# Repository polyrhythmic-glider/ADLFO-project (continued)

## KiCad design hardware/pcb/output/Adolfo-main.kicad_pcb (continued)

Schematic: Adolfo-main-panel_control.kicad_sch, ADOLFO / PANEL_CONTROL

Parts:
R41: 10k; r0805

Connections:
+3V3: R41.2; also elsewhere on the board
OLED_RESET: R41.1; also elsewhere on the board

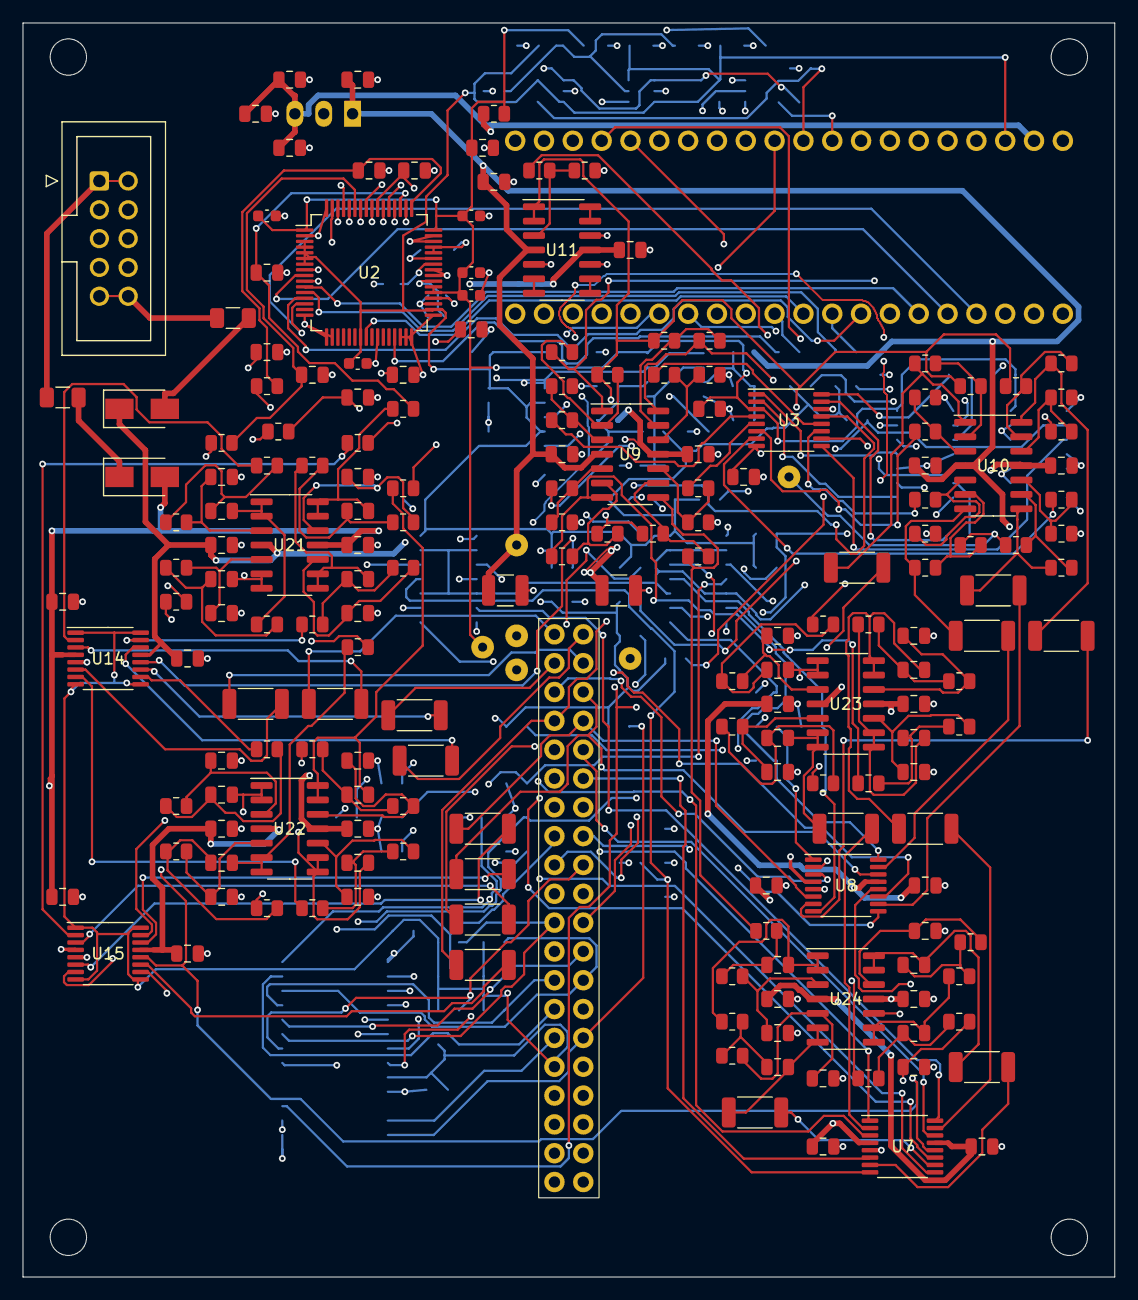
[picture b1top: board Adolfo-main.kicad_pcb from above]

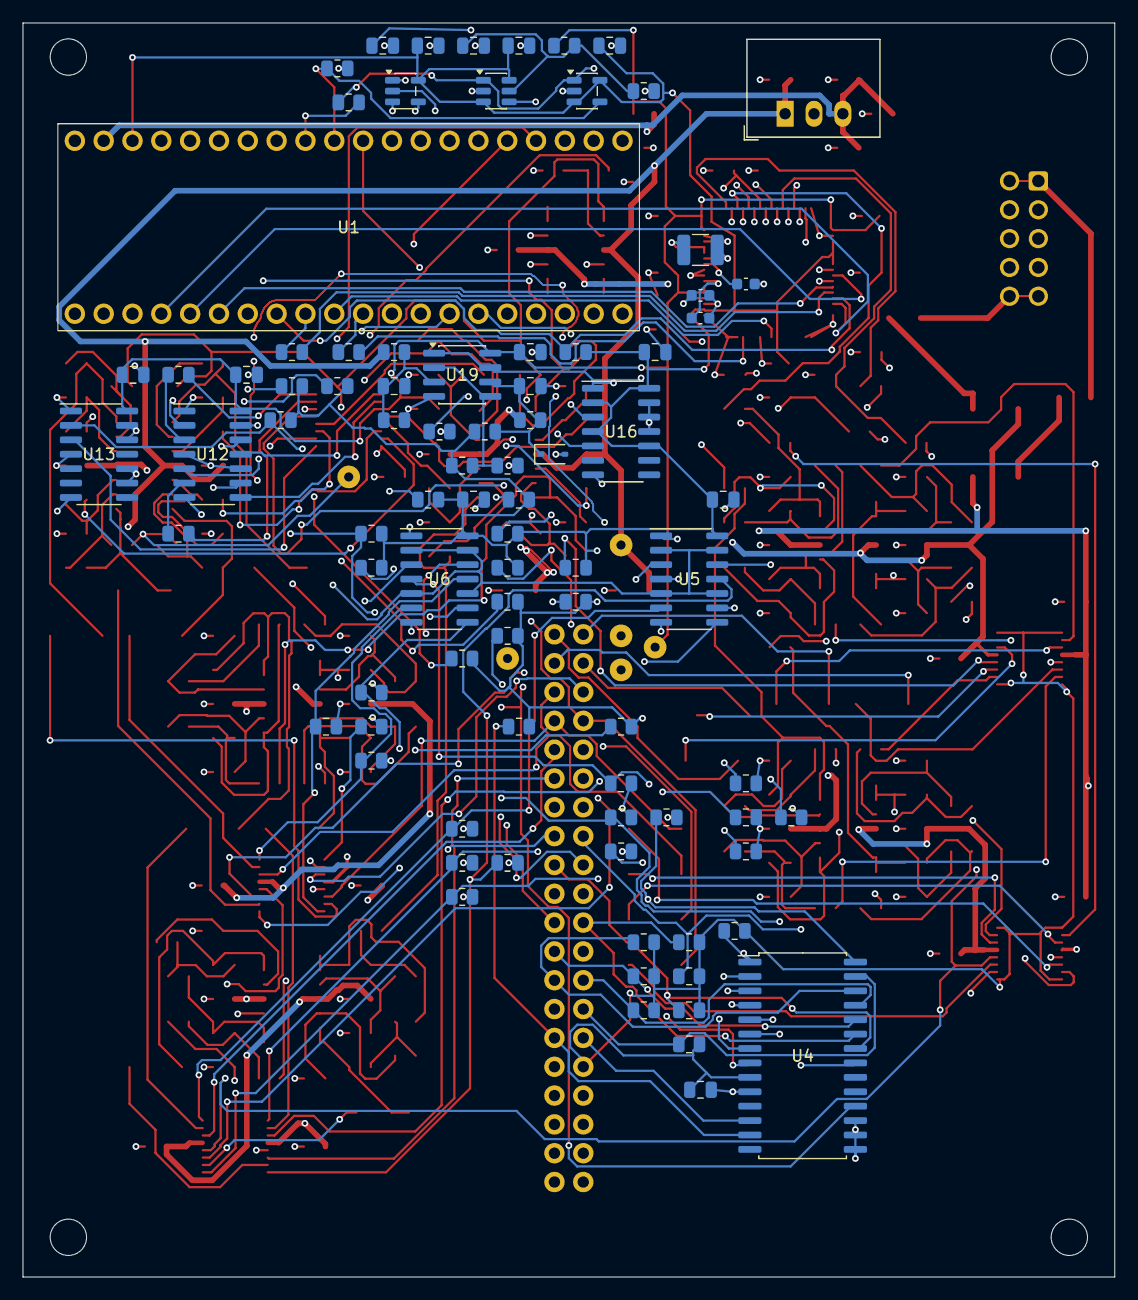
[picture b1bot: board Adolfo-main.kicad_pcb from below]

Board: 4 copper layers, 96.2 x 110.5 mm, 283 parts (87 on the bottom side), 212 nets.

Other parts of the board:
H1, H2, H3, H4: mount

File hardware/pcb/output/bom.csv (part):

Reference,Circuit role,Value / part,Footprint,Board,Side,X,Y,Notes,MPN,Manufacturer,Datasheet
J13,JM,Samtec TSW-120-07-G-D,header40,main,F,50.6,87,,,,
J15,JP,Samtec SSW-120-02-G-D,socket40,panel,B,50.6,87,Mirrored socket numbering mates to JM pin-for-pin.,,,
E1,E1,ALPS EC11E18244AU,encoder,panel,F,17.5,48,,,,
K1,K1,E-Switch TL1105DF160Q,button,panel,F,17.5,67,,,,
J1,J1,IN1 PJ398SM,jack,panel,F,17.5,80,Fixed IN normal grounded for a defined unpatched input; CTRL/OUT normals open to avoid shorting an output.,,,
J2,J2,CTRL1 PJ398SM,jack,panel,F,17.5,95,Fixed IN normal grounded for a defined unpatched input; CTRL/OUT normals open to avoid shorting an output.,,,
J3,J3,OUT1 PJ398SM,jack,panel,F,17.5,110,Fixed IN normal grounded for a defined unpatched input; CTRL/OUT normals open to avoid shorting an output.,,,
E2,E2,ALPS EC11E18244AU,encoder,panel,F,39.5,48,,,,
K2,K2,E-Switch TL1105DF160Q,button,panel,F,39.5,67,,,,
J4,J4,IN2 PJ398SM,jack,panel,F,39.5,80,Fixed IN normal grounded for a defined unpatched input; CTRL/OUT normals open to avoid shorting an output.,,,
J5,J5,CTRL2 PJ398SM,jack,panel,F,39.5,95,Fixed IN normal grounded for a defined unpatched input; CTRL/OUT normals open to avoid shorting an output.,,,
J6,J6,OUT2 PJ398SM,jack,panel,F,39.5,110,Fixed IN normal grounded for a defined unpatched input; CTRL/OUT normals open to avoid shorting an output.,,,
E3,E3,ALPS EC11E18244AU,encoder,panel,F,61.5,48,,,,
K3,K3,E-Switch TL1105DF160Q,button,panel,F,61.5,67,,,,
J7,J7,IN3 PJ398SM,jack,panel,F,61.5,80,Fixed IN normal grounded for a defined unpatched input; CTRL/OUT normals open to avoid shorting an output.,,,
J8,J8,CTRL3 PJ398SM,jack,panel,F,61.5,95,Fixed IN normal grounded for a defined unpatched input; CTRL/OUT normals open to avoid shorting an output.,,,
J9,J9,OUT3 PJ398SM,jack,panel,F,61.5,110,Fixed IN normal grounded for a defined unpatched input; CTRL/OUT normals open to avoid shorting an output.,,,
E4,E4,ALPS EC11E18244AU,encoder,panel,F,83.5,48,,,,
K4,K4,E-Switch TL1105DF160Q,button,panel,F,83.5,67,,,,
J10,J10,IN4 PJ398SM,jack,panel,F,83.5,80,Fixed IN normal grounded for a defined unpatched input; CTRL/OUT normals open to avoid shorting an output.,,,
J11,J11,CTRL4 PJ398SM,jack,panel,F,83.5,95,Fixed IN normal grounded for a defined unpatched input; CTRL/OUT normals open to avoid shorting an output.,,,
J12,J12,OUT4 PJ398SM,jack,panel,F,83.5,110,Fixed IN normal grounded for a defined unpatched input; CTRL/OUT normals open to avoid shorting an output.,,,
J14,J14,"Waveshare 0.96inch OLED Module (D), I2C",oled7,panel,F,50.6,11,"Waveshare module (D), SSD1315, 26 x 26 mm; I2C hardware configuration required. Seven-pin order VCC/GND/DIN/CLK/CS/DC/RES.",,,
U1,U1,Daisy Seed 3,seed,main,B,70,27,Seed 3 40-pin carrier; onboard codec and MCU DAC unused. Verify physical USB access on the assembled stack.,,,
U2,U2,AD7606C-18BSTZ,lqfp64,main,F,33,31,"SOFTWARE mode OS[2:0]=111; select one DOUTA, bipolar ranges, bandwidth per channel. No audio HPF. Register/DMA driver missing.",AD7606C-18BSTZ,Analog Devices,https://www.analog.com/media/en/technical-documentation/data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
U3,U3,DAC8568BPW,tssop16,main,F,70,44,"B grade matters: internal 2.5 V reference, output span 2.5 V, midscale reset; enable reference in software. 16-bit output, not a 24-bit codec.",DAC8568BPW,Texas Instruments,https://www.ti.com/lit/ds/symlink/dac8568.pdf
U4,U4,MCP23017-E/SO,soic28,main,B,30,100,I2C 0x20. Encoders A/B stay on MCU GPIO; only clicks/keys and static output requests use expander.,MCP23017-E/SO,Microchip,https://ww1.microchip.com/downloads/en/DeviceDoc/20001952C.pdf
U5,U5,SN74LVC08ADR,soic14,main,B,40,58,,SN74LVC08ADR,Texas Instruments,https://www.ti.com/lit/ds/symlink/sn74lvc08a.pdf
U6,U6,SN74LVC08ADR,soic14,main,B,62,58,,SN74LVC08ADR,Texas Instruments,https://www.ti.com/lit/ds/symlink/sn74lvc08a.pdf
U7,U7,ADG5412FBRUZ,tssop16,main,F,80,108,Not ADG5413F. IN=0 disconnects. Protected S faces jack; driver on D. Fault/power-off isolation needs bench qualification; not protection against every output collision.,ADG5412FBRUZ,Analog Devices,https://www.analog.com/media/en/technical-documentation/data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
U8,U8,ADG5412FBRUZ,tssop16,main,F,75,85,Not ADG5413F. IN=0 disconnects. Protected S faces jack; driver on D. Fault/power-off isolation needs bench qualification; not protection against every output collision.,ADG5412FBRUZ,Analog Devices,https://www.analog.com/media/en/technical-documentation/data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
RA1,RA1,10k 0.1%,r0805,main,F,50,44,,,,
RB1,RB1,40k 0.1%,r0805,main,F,50,41,,,,
RC1,RC1,10k 0.1%,r0805,main,F,54,40,,,,
RD1,RD1,40k 0.1%,r0805,main,F,50,38,,,,
RO1,RO1,1k 1W 1%,r2010,main,F,75,80,Limits fault current; specify/calibrate the intended load. Not a load-independent pitch output.,CRCW20101K00FKEFHP,Vishay,https://www.vishay.com/docs/20043/crcwhpe3.pdf
RE1,RE1,100k,r0805,main,B,60,83,,,,
RQ1,RQ1,100k,r0805,main,B,35,79,,,,
RA2,RA2,10k 0.1%,r0805,main,F,50,50,,,,
RB2,RB2,40k 0.1%,r0805,main,F,50,53,,,,
RC2,RC2,10k 0.1%,r0805,main,F,54,54,,,,
RD2,RD2,40k 0.1%,r0805,main,F,50,56,,,,
RO2,RO2,1k 1W 1%,r2010,main,F,82,80,Limits fault current; specify/calibrate the intended load. Not a load-independent pitch output.,CRCW20101K00FKEFHP,Vishay,https://www.vishay.com/docs/20043/crcwhpe3.pdf
RE2,RE2,100k,r0805,main,B,60,80,,,,
RQ2,RQ2,100k,r0805,main,B,35,76,,,,
RA3,RA3,10k 0.1%,r0805,main,F,62,50,,,,
RB3,RB3,40k 0.1%,r0805,main,F,62,53,,,,
RC3,RC3,10k 0.1%,r0805,main,F,58,54,,,,
RD3,RD3,40k 0.1%,r0805,main,F,62,56,,,,
RO3,RO3,1k 1W 1%,r2010,main,F,67,105,Limits fault current; specify/calibrate the intended load. Not a load-independent pitch output.,CRCW20101K00FKEFHP,Vishay,https://www.vishay.com/docs/20043/crcwhpe3.pdf
RE3,RE3,100k,r0805,main,B,60,86,,,,
RQ3,RQ3,100k,r0805,main,B,35,82,,,,
RA4,RA4,10k 0.1%,r0805,main,F,59,40,,,,
RB4,RB4,40k 0.1%,r0805,main,F,63,40,,,,
RC4,RC4,10k 0.1%,r0805,main,F,59,37,,,,
RD4,RD4,40k 0.1%,r0805,main,F,63,37,,,,
RO4,RO4,1k 1W 1%,r2010,main,F,87,101,Limits fault current; specify/calibrate the intended load. Not a load-independent pitch output.,CRCW20101K00FKEFHP,Vishay,https://www.vishay.com/docs/20043/crcwhpe3.pdf
RE4,RE4,100k,r0805,main,B,56,83,,,,
RQ4,RQ4,100k,r0805,main,B,31,79,,,,
RA5,RA5,10k 0.1%,r0805,main,F,82,45,,,,
RB5,RB5,40k 0.1%,r0805,main,F,82,42,,,,
RC5,RC5,10k 0.1%,r0805,main,F,86,41,,,,
RD5,RD5,40k 0.1%,r0805,main,F,82,39,,,,
RO5,RO5,1k 1W 1%,r2010,main,F,76,57,Limits fault current; specify/calibrate the intended load. Not a load-independent pitch output.,CRCW20101K00FKEFHP,Vishay,https://www.vishay.com/docs/20043/crcwhpe3.pdf
RE5,RE5,100k,r0805,main,B,68,71,,,,
RQ5,RQ5,100k,r0805,main,B,46,79,,,,
RA6,RA6,10k 0.1%,r0805,main,F,82,51,,,,
RB6,RB6,40k 0.1%,r0805,main,F,82,54,,,,
RC6,RC6,10k 0.1%,r0805,main,F,86,55,,,,
RD6,RD6,40k 0.1%,r0805,main,F,82,57,,,,
RO6,RO6,1k 1W 1%,r2010,main,F,87,63,Limits fault current; specify/calibrate the intended load. Not a load-independent pitch output.,CRCW20101K00FKEFHP,Vishay,https://www.vishay.com/docs/20043/crcwhpe3.pdf
RE6,RE6,100k,r0805,main,B,68,74,,,,
RQ6,RQ6,100k,r0805,main,B,46,76,,,,
RA7,RA7,10k 0.1%,r0805,main,F,94,51,,,,
RB7,RB7,40k 0.1%,r0805,main,F,94,54,,,,
RC7,RC7,10k 0.1%,r0805,main,F,90,55,,,,
RD7,RD7,40k 0.1%,r0805,main,F,94,57,,,,
RO7,RO7,1k 1W 1%,r2010,main,F,88,59,Limits fault current; specify/calibrate the intended load. Not a load-independent pitch output.,CRCW20101K00FKEFHP,Vishay,https://www.vishay.com/docs/20043/crcwhpe3.pdf
RE7,RE7,100k,r0805,main,B,68,68,,,,
RQ7,RQ7,100k,r0805,main,B,46,82,,,,
RA8,RA8,10k 0.1%,r0805,main,F,94,45,,,,
RB8,RB8,40k 0.1%,r0805,main,F,94,42,,,,
RC8,RC8,10k 0.1%,r0805,main,F,90,41,,,,
RD8,RD8,40k 0.1%,r0805,main,F,94,39,,,,
RO8,RO8,1k 1W 1%,r2010,main,F,94,63,Limits fault current; specify/calibrate the intended load. Not a load-independent pitch output.,CRCW20101K00FKEFHP,Vishay,https://www.vishay.com/docs/20043/crcwhpe3.pdf
RE8,RE8,100k,r0805,main,B,72,71,,,,
RQ8,RQ8,100k,r0805,main,B,42,79,,,,
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
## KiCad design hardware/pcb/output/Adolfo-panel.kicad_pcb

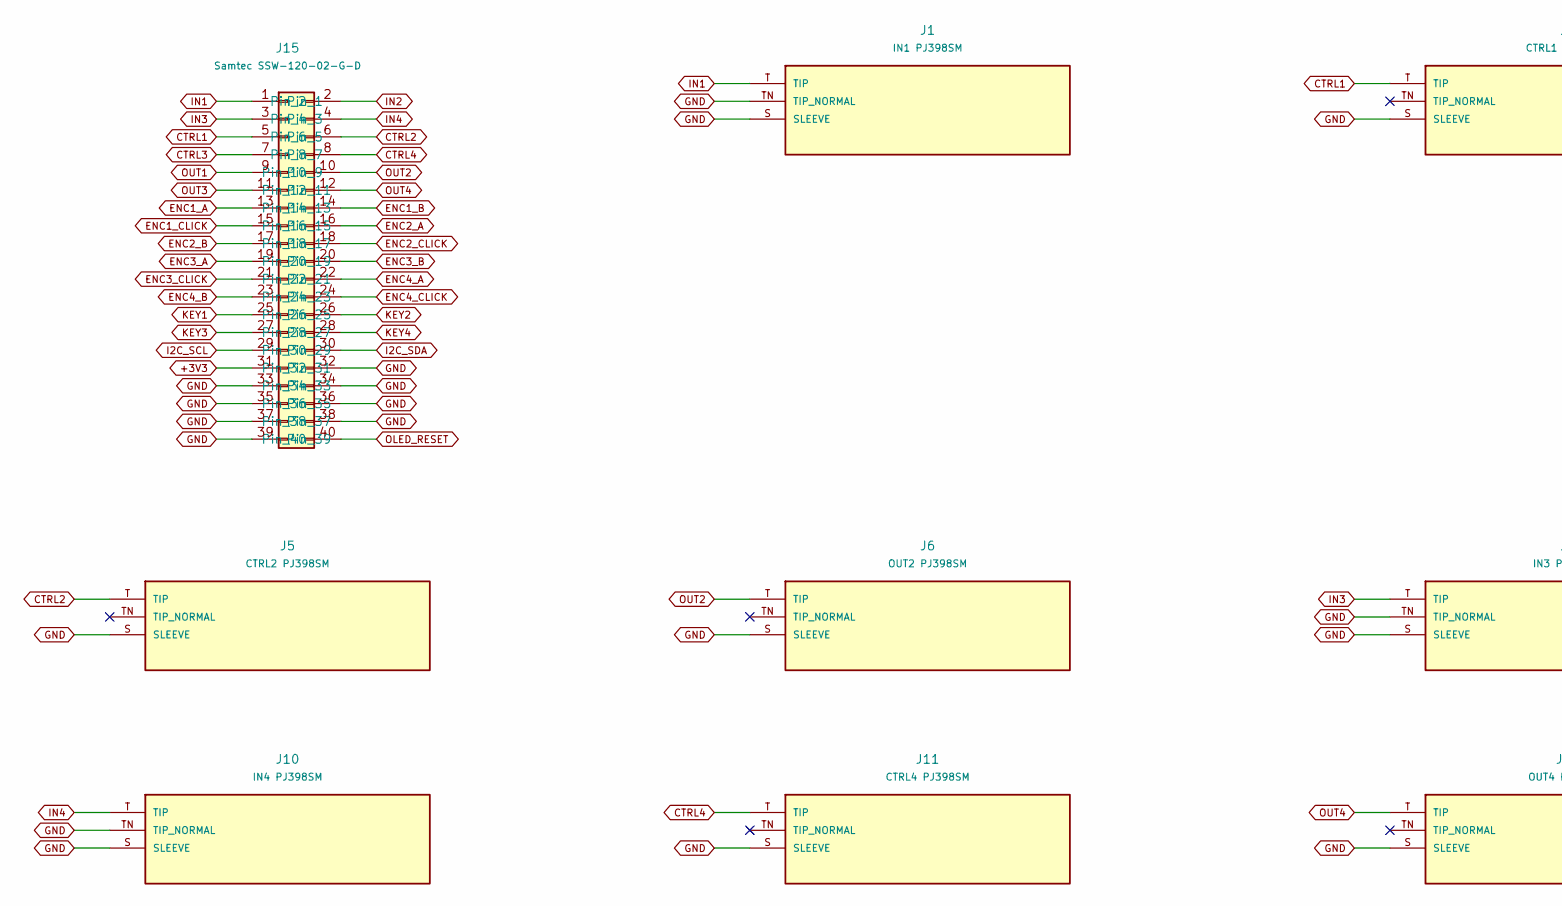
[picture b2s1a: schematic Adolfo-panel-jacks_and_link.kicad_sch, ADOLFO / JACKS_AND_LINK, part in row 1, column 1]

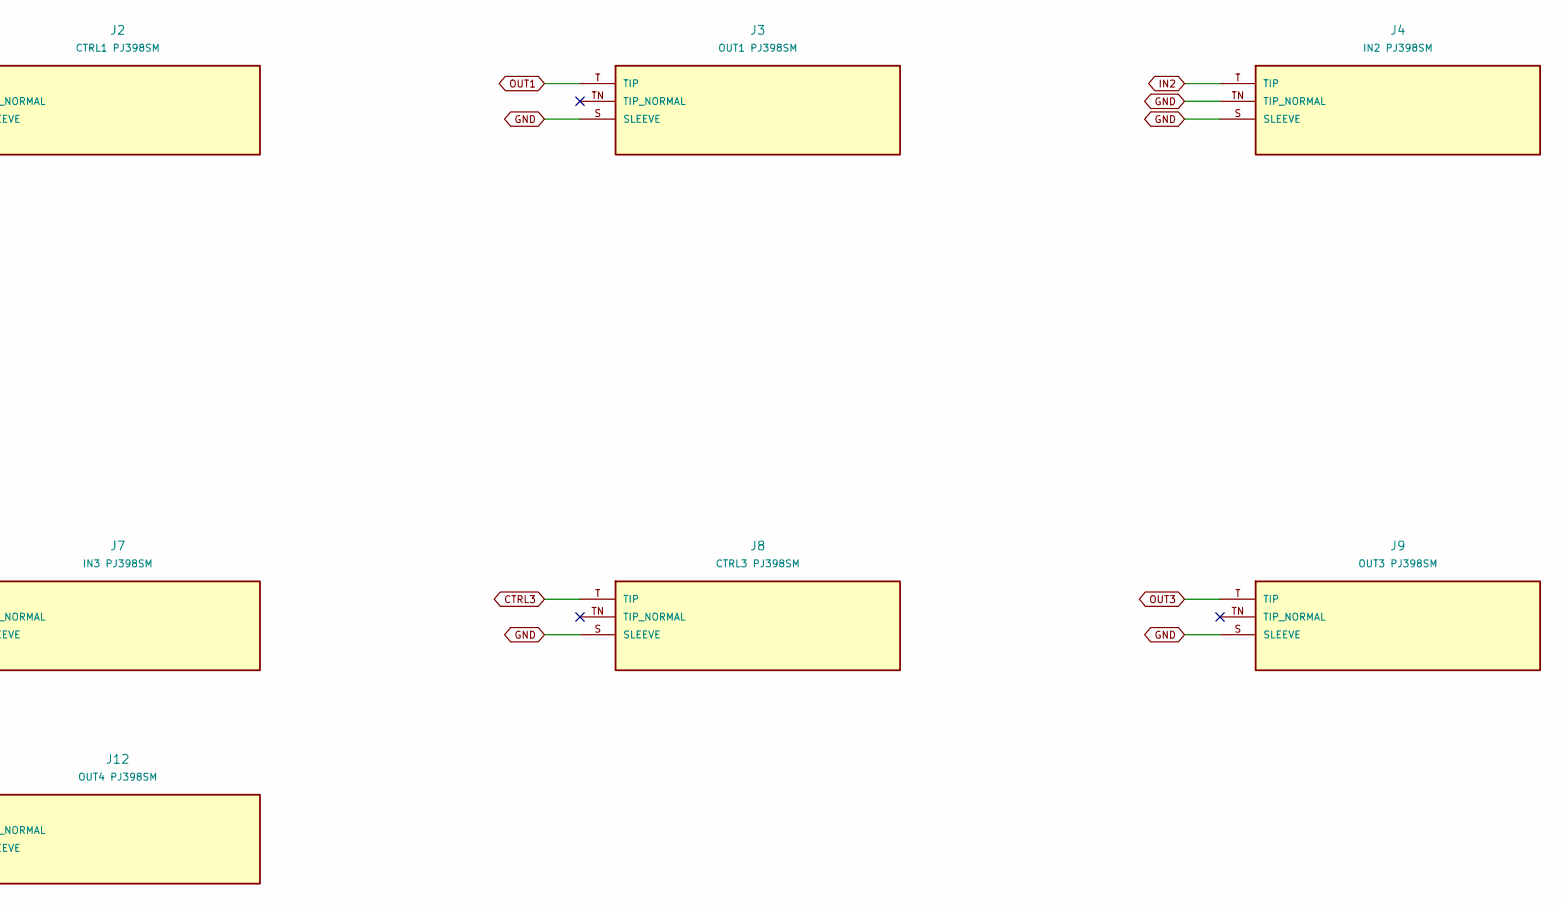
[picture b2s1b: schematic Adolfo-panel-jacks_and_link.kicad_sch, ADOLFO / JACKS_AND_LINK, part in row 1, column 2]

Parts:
J1: IN1 PJ398SM; jack
J2: CTRL1 PJ398SM; jack
J3: OUT1 PJ398SM; jack
J4: IN2 PJ398SM; jack
J5: CTRL2 PJ398SM; jack
J6: OUT2 PJ398SM; jack
J7: IN3 PJ398SM; jack
J8: CTRL3 PJ398SM; jack
J9: OUT3 PJ398SM; jack
J10: IN4 PJ398SM; jack
J11: CTRL4 PJ398SM; jack
J12: OUT4 PJ398SM; jack
J15: Samtec SSW-120-02-G-D; socket40

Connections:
+3V3: J15.31; also elsewhere on the board
CTRL1: J2.T (TIP), J15.5
CTRL2: J5.T (TIP), J15.6
CTRL3: J8.T (TIP), J15.7
CTRL4: J11.T (TIP), J15.8
ENC1_A: J15.13; also elsewhere on the board
ENC1_B: J15.14; also elsewhere on the board
ENC1_CLICK: J15.15; also elsewhere on the board
ENC2_A: J15.16; also elsewhere on the board
ENC2_B: J15.17; also elsewhere on the board
ENC2_CLICK: J15.18; also elsewhere on the board
ENC3_A: J15.19; also elsewhere on the board
ENC3_B: J15.20; also elsewhere on the board
ENC3_CLICK: J15.21; also elsewhere on the board
ENC4_A: J15.22; also elsewhere on the board
ENC4_B: J15.23; also elsewhere on the board
ENC4_CLICK: J15.24; also elsewhere on the board
GND: J1.S (SLEEVE), J1.TN (TIP_NORMAL), J2.S (SLEEVE), J3.S (SLEEVE), J4.S (SLEEVE), J4.TN (TIP_NORMAL), J5.S (SLEEVE), J6.S (SLEEVE), J7.S (SLEEVE), J7.TN (TIP_NORMAL), J8.S (SLEEVE), J9.S (SLEEVE), J10.S (SLEEVE), J10.TN (TIP_NORMAL), J11.S (SLEEVE), J12.S (SLEEVE), J15.32, J15.33, J15.34, J15.35, J15.36, J15.37, J15.38, J15.39; also elsewhere on the board
I2C_SCL: J15.29; also elsewhere on the board
I2C_SDA: J15.30; also elsewhere on the board
IN1: J1.T (TIP), J15.1
IN2: J4.T (TIP), J15.2
IN3: J7.T (TIP), J15.3
IN4: J10.T (TIP), J15.4
KEY1: J15.25; also elsewhere on the board
KEY2: J15.26; also elsewhere on the board
KEY3: J15.27; also elsewhere on the board
KEY4: J15.28; also elsewhere on the board
OLED_RESET: J15.40; also elsewhere on the board
OUT1: J3.T (TIP), J15.9
OUT2: J6.T (TIP), J15.10
OUT3: J9.T (TIP), J15.11
OUT4: J12.T (TIP), J15.12

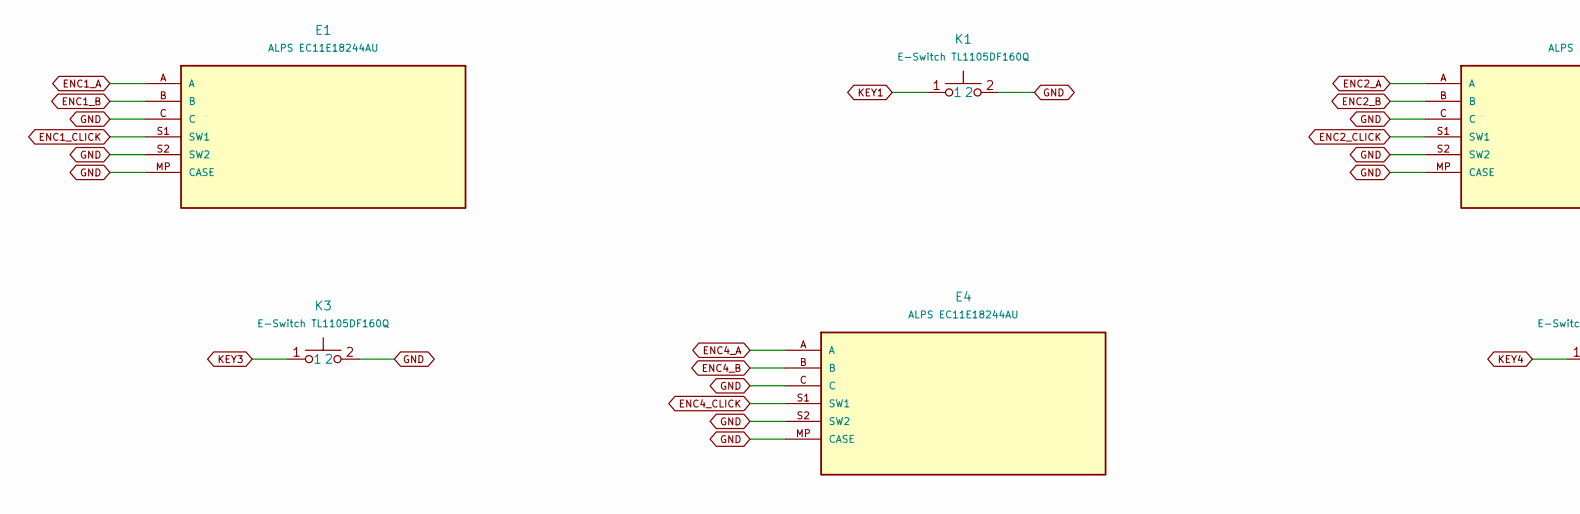
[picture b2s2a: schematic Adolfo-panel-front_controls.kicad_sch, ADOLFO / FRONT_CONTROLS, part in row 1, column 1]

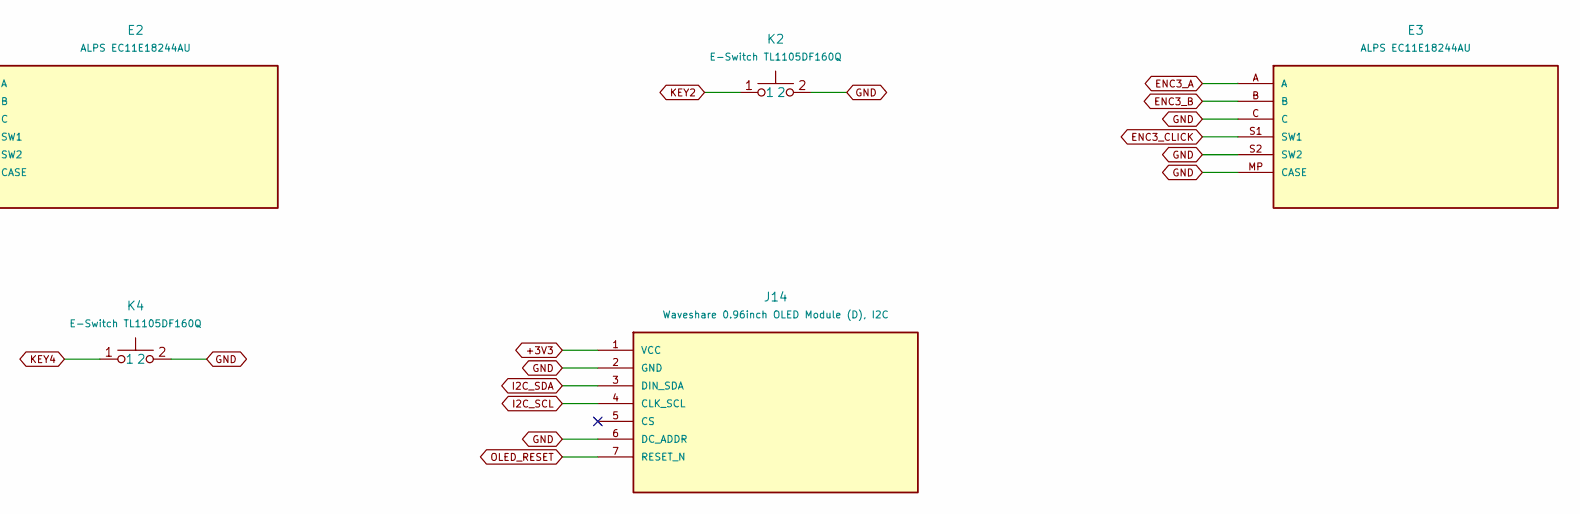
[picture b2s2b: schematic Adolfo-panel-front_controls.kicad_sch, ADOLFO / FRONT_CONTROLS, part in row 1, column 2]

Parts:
E1, E2, E3, E4: ALPS EC11E18244AU; encoder
J14: Waveshare 0.96inch OLED Module (D), I2C; oled7
K1, K2, K3, K4: E-Switch TL1105DF160Q; button

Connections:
+3V3: J14.1 (VCC); also elsewhere on the board
ENC1_A: E1.A; also elsewhere on the board
ENC1_B: E1.B; also elsewhere on the board
ENC1_CLICK: E1.S1 (SW1); also elsewhere on the board
ENC2_A: E2.A; also elsewhere on the board
ENC2_B: E2.B; also elsewhere on the board
ENC2_CLICK: E2.S1 (SW1); also elsewhere on the board
ENC3_A: E3.A; also elsewhere on the board
ENC3_B: E3.B; also elsewhere on the board
ENC3_CLICK: E3.S1 (SW1); also elsewhere on the board
ENC4_A: E4.A; also elsewhere on the board
ENC4_B: E4.B; also elsewhere on the board
ENC4_CLICK: E4.S1 (SW1); also elsewhere on the board
GND: E1.C, E1.MP (CASE), E1.S2 (SW2), E2.C, E2.MP (CASE), E2.S2 (SW2), E3.C, E3.MP (CASE), E3.S2 (SW2), E4.C, E4.MP (CASE), E4.S2 (SW2), J14.2 (GND), J14.6 (DC_ADDR), K1.2, K2.2, K3.2, K4.2; also elsewhere on the board
I2C_SCL: J14.4 (CLK_SCL); also elsewhere on the board
I2C_SDA: J14.3 (DIN_SDA); also elsewhere on the board
KEY1: K1.1; also elsewhere on the board
KEY2: K2.1; also elsewhere on the board
KEY3: K3.1; also elsewhere on the board
KEY4: K4.1; also elsewhere on the board
OLED_RESET: J14.7 (RESET_N); also elsewhere on the board

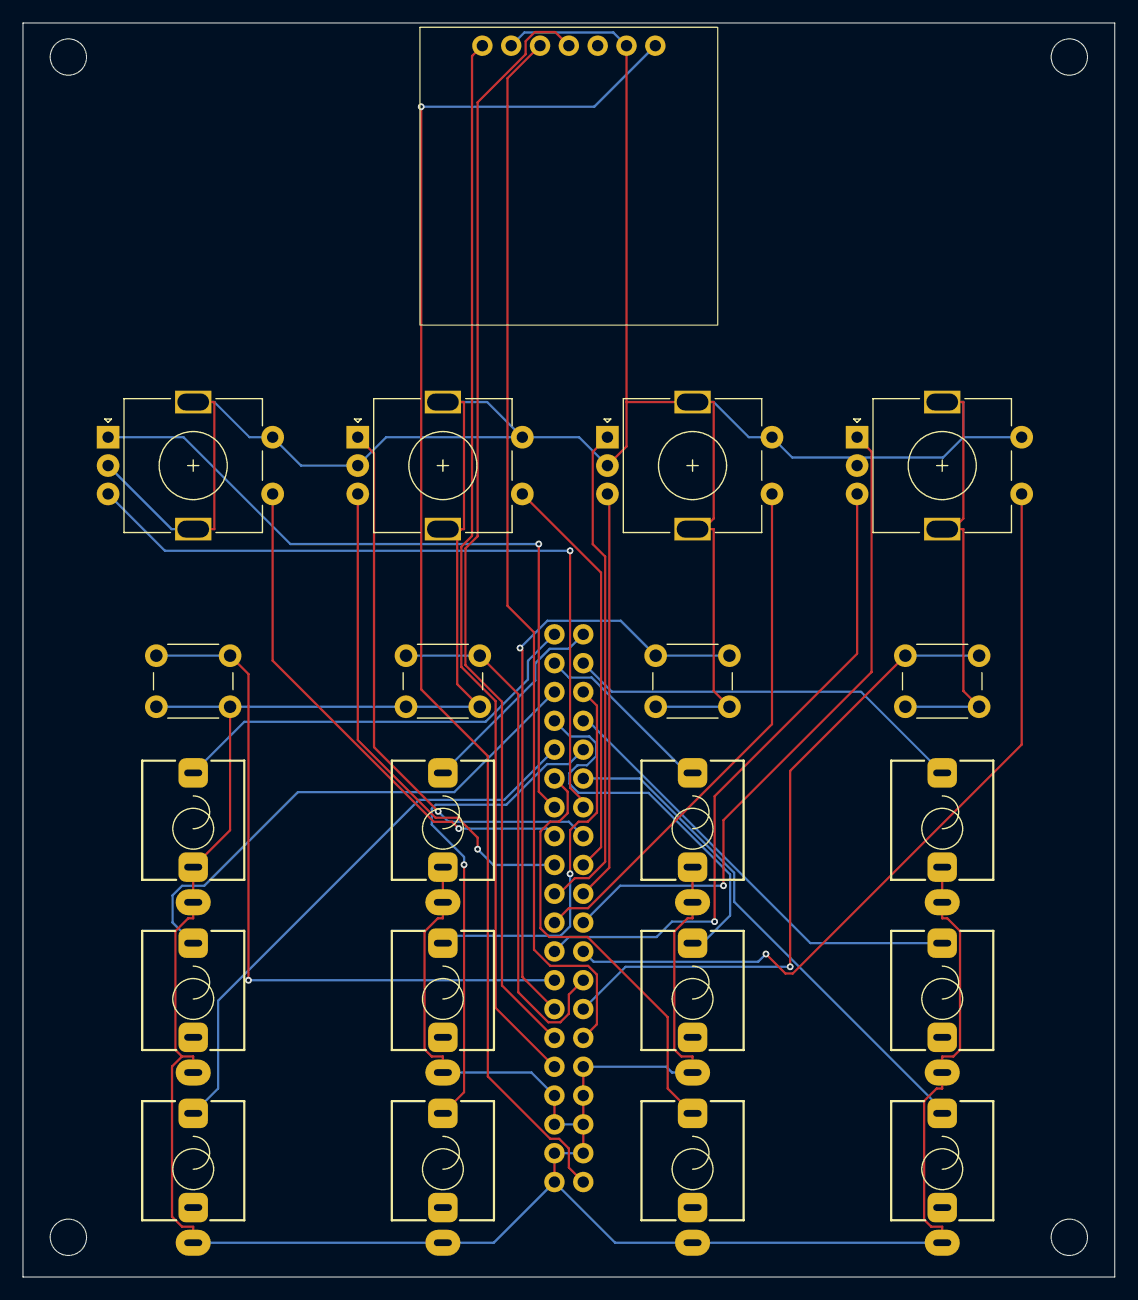
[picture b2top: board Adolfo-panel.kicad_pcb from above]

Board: 2 copper layers, 96.2 x 110.5 mm, 26 parts (1 on the bottom side), 33 nets.

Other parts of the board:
H1, H2, H3, H4: mount

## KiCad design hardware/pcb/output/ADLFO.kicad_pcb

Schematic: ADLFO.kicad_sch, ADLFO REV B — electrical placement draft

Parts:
C1, C2: 10uF 50V X7R; c0805
C3, C4, C6: 10uF 10V X7R; c0805
C5, C7, C11, C12: 100nF; c0805
C8, C9: 100nF 50V; c0805
C10: 47uF 10V low ESR candidate; radial_cap
C101, C201, C301, C401: 10nF; c0805
C102, C202, C302, C402: 1nF; c0805
D1, D2, D3: SS14; sma
D101, D201, D301, D401: 1N4148W; sod123
D102, D202, D302, D402: BAT54S; sot23
ENC1: RISE; encoder
ENC2: FALL; encoder
ENC3: SYMMETRY; encoder
ENC4: LEVEL; encoder
F1: PTC 0.5A hold candidate; ptc1812
J1: TRIG1; jack
J2: CV1; jack
J3: OUT1; jack
J4: TRIG2; jack
J5: CV2; jack
J6: OUT2; jack
J7: TRIG3; jack
J8: CV3; jack
J9: OUT3; jack
J10: TRIG4; jack
J11: CV4; jack
J12: OUT4; jack
J13: EURORACK 2x5 keyed; idc10
J14: OLED SSD1306 128x64; oled
Q1, Q2, Q3, Q4: MMBT3904; sot23
R1, R2: 4.7k DNP; r0805
R101, R201, R301, R401: 100k; r0805
R102, R202, R302, R402: 1M; r0805
R103, R203, R303, R403: 47k; r0805
R104, R204, R304, R404: 100k 0.1%; r0805
R105, R205, R305, R405: 33k 0.1%; r0805
R106, R108, R206, R208, R306, R308, R406, R408: 10k; r0805
R107, R207, R307, R407: 1k; r0805
R109, R209, R309, R409: 10k 0.1%; r0805
R110, R210, R310, R410: 15k 0.1%; r0805
R111, R211, R311, R411: 2.2k 0.5W; r2010
RP11, RP12, RP13, RP14, RP21, RP22, RP23, RP24, RP31, RP32, RP33, RP34, RP41, RP42, RP43, RP44: 10k DNP; r0805
SW1: CH 1; button
SW2: CH 2; button
SW3: CH 3; button
SW4: CH 4; button
TP1: GND; testpoint
TP2: +12VA; testpoint
TP3: -12VA; testpoint
TP4: +5V_SEED; testpoint
TP5: +3V3; testpoint
TP11: DAC1; testpoint
TP12: DAC2; testpoint
TP13: DAC3; testpoint
TP14: DAC4; testpoint
U1: Daisy Seed (socketed); seed
U2: Adafruit MCP4728 STEMMA QT breakout; mcp4728_breakout
U3: MCP6004-I/SL; soic14
U4: TL074CDR; soic14
U5: R-78E5.0-0.5; recom

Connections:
+3V3: C5.1, C6.1, C7.1, C12.1, D102.2, D202.2, D302.2, D402.2, J14.2, R1.1, R2.1, R103.1, R203.1, R303.1, R403.1, RP11.1, RP12.1, RP13.1, RP14.1, RP21.1, RP22.1, RP23.1, RP24.1, RP31.1, RP32.1, RP33.1, RP34.1, RP41.1, RP42.1, RP43.1, RP44.1, TP5.1, U1.38 (+3V3), U2.1 (JP1_VCC), U2.12 (JP2_VCC), U3.4
+5V_REG: C3.1, D3.2, U5.3
+5V_SEED: C4.1, C10.1, C11.1, D3.1, TP4.1, U1.39 (+5V_SEED)
+12VA: C1.1, C8.1, D1.1, TP2.1, U4.4, U5.1
+12V_FUSED: D1.2, F1.2
+12V_IN: F1.1, J13.9, J13.10
-12VA: C2.2, C9.1, D2.2, TP3.1, U4.11
-12V_IN: D2.1, J13.1, J13.2
CV1: J2.T, R104.1
CV2: J5.T, R204.1
CV3: J8.T, R304.1
CV4: J11.T, R404.1
CV_BUF1: R107.1, U3.1, U3.2
CV_BUF2: R207.1, U3.6, U3.7
CV_BUF3: R307.1, U3.8, U3.9
CV_BUF4: R407.1, U3.13, U3.14
CV_CLAMP1: D102.3, R106.2, U3.3
CV_CLAMP2: D202.3, R206.2, U3.5
CV_CLAMP3: D302.3, R306.2, U3.10
CV_CLAMP4: D402.3, R406.2, U3.12
CV_DIV1: C101.1, R104.2, R105.1, R106.1
CV_DIV2: C201.1, R204.2, R205.1, R206.1
CV_DIV3: C301.1, R304.2, R305.1, R306.1
CV_DIV4: C401.1, R404.2, R405.1, R406.1
D0: ENC1.A, RP11.2, U1.1 (D0)
D1: ENC1.B, RP12.2, U1.2 (D1)
D2: ENC1.S1, RP13.2, U1.3 (D2)
D3: ENC2.A, RP21.2, U1.4 (D3)
D4: ENC2.B, RP22.2, U1.5 (D4)
D5: ENC2.S1, RP23.2, U1.6 (D5)
D6: Q1.3, R103.2, U1.7 (D6)
D7: ENC3.A, RP31.2, U1.8 (D7)
D8: ENC3.B, RP32.2, U1.9 (D8)
D9: ENC3.S1, RP33.2, U1.10 (D9)
D10: ENC4.A, RP41.2, U1.11 (D10)
D11: J14.3, R1.2, U1.12 (D11), U2.3 (JP1_SCL)
D12: J14.4, R2.2, U1.13 (D12), U2.4 (JP1_SDA)
D13: ENC4.B, RP42.2, U1.14 (D13)
D14: ENC4.S1, RP43.2, U1.15 (D14)
D15: C102.1, R107.2, U1.22 (D15)
D16: C202.1, R207.2, U1.23 (D16)
D17: C302.1, R307.2, U1.24 (D17)
D18: C402.1, R407.2, U1.25 (D18)
D19: Q2.3, R203.2, U1.26 (D19)
D20: Q3.3, R303.2, U1.27 (D20)
D21: Q4.3, R403.2, U1.28 (D21)
D24: RP24.2, SW2.1, U1.31 (D24)
D25: RP14.2, SW1.1, U1.32 (D25)
D26: RP34.2, SW3.1, U1.33 (D26)
D27: RP44.2, SW4.1, U1.34 (D27)
DAC1: R108.1, TP11.1, U2.8 (JP2_VA)
DAC2: R208.1, TP12.1, U2.9 (JP2_VB)
DAC3: R308.1, TP13.1, U2.10 (JP2_VC)
DAC4: R408.1, TP14.1, U2.11 (JP2_VD)
GND: C1.2, C2.1, C3.2, C4.2, C5.2, C6.2, C7.2, C8.2, C9.2, C10.2, C11.2, C12.2, C101.2, C102.2, C201.2, C202.2, C301.2, C302.2, C401.2, C402.2, D101.2, D102.1, D201.2, D202.1, D301.2, D302.1, D401.2, D402.1, ENC1.C, ENC1.MP, ENC1.S2, ENC2.C, ENC2.MP, ENC2.S2, ENC3.C, ENC3.MP, ENC3.S2, ENC4.C, ENC4.MP, ENC4.S2, J1.S, J1.TN, J2.S, J2.TN, J3.S, J4.S, J4.TN, J5.S, J5.TN, J6.S, J7.S, J7.TN, J8.S, J8.TN, J9.S, J10.S, J10.TN, J11.S, J11.TN, J12.S, J13.3, J13.4, J13.5, J13.6, J13.7, J13.8, J14.1, Q1.2, Q2.2, Q3.2, Q4.2, R102.2, R105.2, R109.2, R202.2, R205.2, R209.2, R302.2, R305.2, R309.2, R402.2, R405.2, R409.2, SW1.2, SW2.2, SW3.2, SW4.2, TP1.1, U1.20 (GND), U1.40 (GND), U2.2 (JP1_GND), U2.5 (JP1_LDAC), U2.7 (JP2_GND), U3.11, U5.2
OUT1: J3.T, R111.2
OUT2: J6.T, R211.2
OUT3: J9.T, R311.2
OUT4: J12.T, R411.2
OUT_AMP1: R110.1, R111.1, U4.1
OUT_AMP2: R210.1, R211.1, U4.7
OUT_AMP3: R310.1, R311.1, U4.8
OUT_AMP4: R410.1, R411.1, U4.14
OUT_FB1: R109.1, R110.2, U4.2
OUT_FB2: R209.1, R210.2, U4.6
OUT_FB3: R309.1, R310.2, U4.9
OUT_FB4: R409.1, R410.2, U4.13
OUT_PLUS1: R108.2, U4.3
OUT_PLUS2: R208.2, U4.5
OUT_PLUS3: R308.2, U4.10
OUT_PLUS4: R408.2, U4.12
TRIG1: J1.T, R101.1
TRIG2: J4.T, R201.1
TRIG3: J7.T, R301.1
TRIG4: J10.T, R401.1
TRIG_BASE1: D101.1, Q1.1, R101.2, R102.1
TRIG_BASE2: D201.1, Q2.1, R201.2, R202.1
TRIG_BASE3: D301.1, Q3.1, R301.2, R302.1
TRIG_BASE4: D401.1, Q4.1, R401.2, R402.1

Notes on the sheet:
SYSTEM / terminal net schematic
CH1 / terminal net schematic
CH2 / terminal net schematic
CH3 / terminal net schematic
CH4 / terminal net schematic

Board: 2 copper layers, 138 parts (113 on the bottom side), 79 nets, no tracks yet.

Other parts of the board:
H1, H2, H3, H4: M3 spacer; mount

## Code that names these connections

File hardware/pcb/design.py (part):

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OLED = dict(x=PANEL['width']/2, y=22.5, width=22.2, height=11.6, header_y=11)
RAIL_SLOTS = [(7.5,3),(93.86,3),(7.5,125.5),(93.86,125.5)]
# New board ONLY. SPI assignments checked against libDaisy per/spi.cpp.
PINS = dict(DAC_SYNC=0,DAC_LDAC=1,DAC_SCK=2,ADC_BUSY=3,ADC_CONVST=4,
            ADC_RESET=5,DAC_MOSI=6,ADC_CS=7,ADC_SCK=8,ADC_MISO=9,
            ADC_MOSI=10,I2C_SCL=11,I2C_SDA=12,DAC_CLR=13,OUTPUT_PERMIT=14,
            ENC1_A=15,ENC1_B=16,ENC2_A=17,ENC2_B=18,
            ENC3_A=19,ENC3_B=20,ENC4_A=21,ENC4_B=22,IO_RESET=23,
            WATCHDOG=24,FAULT_N=25,OLED_RESET=26)
PORTS = ([dict(id=f'IN{i}',direction='input',adc=i-1,modes=['audio','cv','gate','trigger']) for i in range(1,5)]
       + [dict(id=f'OUT{i}',direction='output',dac=i-1,modes=['audio','cv','envelope','lfo','gate','trigger']) for i in range(1,5)]
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    for bank,x in enumerate([45,67]):
        pins={7:'GND',14:'+3V3'}
        for j,(a,b,y) in enumerate([(1,2,3),(4,5,6),(9,10,8),(12,13,11)]):
            n=bank*4+j+1;pins.update({a:f'REQ{n}',b:'OUTPUT_PERMIT',y:f'SW_ON{n}'})
        add(f'U{5+bank}','SN74LVC08A candidate','soic14',x,74,pins)
    # Source terminals face jacks; only sources have the quoted fault protection.
    for bank,x in enumerate([45,67]):
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        two(f'RO{n}','100R 0.25W candidate',x,83,f'AMP{n}',f'DRIVE{n}')
        two(f'RE{n}','100k',x,93,f'SW_ON{n}','GND')
        two(f'RQ{n}','100k',x,96,f'REQ{n}','GND')
    quadpins[2].update({3:'REF_HALF',2:'REF_BUF',1:'REF_BUF'})
    for plus,minus,out in [(5,6,7),(10,9,8),(12,13,14)]:quadpins[2].update({plus:'GND',minus:f'UNUSED_FB{out}',out:f'UNUSED_FB{out}'})
    for i,x in enumerate([13,45,80]):
        add(f'U{9+i}','OPA4197ID candidate','soic14',x,60,quadpins[i],note='Candidate: verify offset, stability, noise, output protection and matched ratios. 4*Vdac - 4*Vref gives approximately +/-5 V.')
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        if p['ref']=='UREG':p['note']='RECOM R-78E5.0-1.0, 8-28 V input, 5 V/1 A output, SIP3; max capacitive load 220 uF.'
    # The display header has seven real pins. Fit the module jumpers for I2C, address 0x3c.
    byref['J14']['footprint']='oled7'
    byref['J14']['pins']={'1':'+3V3','2':'GND','3':'I2C_SDA','4':'I2C_SCL','5':None,'6':'GND','7':'OLED_RESET'}
    byref['J14']['note']='Waveshare module (D), SSD1315, 26 x 26 mm; I2C hardware configuration required. Seven-pin order VCC/GND/DIN/CLK/CS/DC/RES.'
    # Hardware watchdog and a fault latch: recovery never silently re-enables the outputs.
    add('U16','SN74HCS74DR','soic14',{1:'SAFE_CLEAR_N',2:'+3V3',3:'OUTPUT_PERMIT',4:'+3V3',5:'SAFE_LATCH',6:None,7:'GND',
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    for ref in ('U5','U6'):
        p=byref[ref]['pins']
        for pin,net in list(p.items()):
            if net=='OUTPUT_PERMIT':p[pin]='SAFE_PERMIT'
    for ref in ('U7','U8'):byref[ref]['pins']['12']='SAFE_CLEAR_N'
    # Protection on both sets of inputs also isolates externally driven jacks when power is absent.
    for bank in range(2):
        pins={4:'-12VA',5:'GND',12:'SAFE_CLEAR_N',13:'+12VA'}
        for j,(ctl,drain,source) in enumerate([(1,2,3),(16,15,14),(9,10,11),(8,7,6)]):
            n=bank*4+j+1;pins.update({ctl:'+3V3',drain:f'PROTECTED{n}',source:f'INPUT_LIMIT{n}'})
        add(f'U{14+bank}','ADG5412FBRUZ','tssop16',pins,'INPUT_PROTECTION')
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        p=cap(ref,'22uF 25V X7R',rail,'POWER');p['footprint']='c1210'
    cap('CREGIN','100nF 50V','+12VA','POWER');cap('CREGOUT','100nF','+5D','POWER')
    two('RRESET_OLED','10k','OLED_RESET','+3V3','PANEL_CONTROL')
    for signal,pin in [('ADC_SCK',12),('ADC_MOSI',29)]:
        byref['U2']['pins'][str(pin)]=signal+'_TERM'
        two('R'+signal,'33R',signal,signal+'_TERM','ADC')
    for signal,buffer_pin in [('DAC_SCK',3),('DAC_MOSI',6)]:
        byref['U12']['pins'][str(buffer_pin)]=signal+'_BUFFER'
        two('R'+signal,'33R',signal+'_BUFFER',signal+'_5V','DAC')
    for ref in ('RSCL','RSDA'):byref[ref]['value']='2.2k'
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
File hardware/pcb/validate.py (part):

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    check(byid['U16']['value']=='SN74HCS74DR','Schmitt-input fault latch tolerates open-drain reset edges')
    check(all(p['mpn']=='CRCW20101K00FKEFHP' and p['value']=='1k 1W 1%' for p in parts if p['footprint']=='r2010'),'All sixteen jack protection resistors specified for 1 W')
    check('DAC8568B' in byid['U3']['value'] and byid['U3']['footprint']=='tssop16','Gain-one midscale-reset DAC8568B')
    check(pins('U3')=={'1':'DAC_LDAC_5V','2':'DAC_SYNC_5V','3':'+5A','4':'DAC1','5':'DAC3','6':'DAC5','7':'DAC7','8':'REF2V5','9':'DAC_CLR_5V','10':'DAC8','11':'DAC6','12':'DAC4','13':'DAC2','14':'GND','15':'DAC_MOSI_5V','16':'DAC_SCK_5V'},'DAC pinout and shifted 5 V logic')
    check(byid['U4']['footprint']=='soic28' and all(pins('U4')[str(k)]==v for k,v in {9:'+3V3',10:'GND',12:'I2C_SCL',13:'I2C_SDA',8:'REQ7',28:'REQ8',21:'ENC1_CLICK',24:'ENC4_CLICK'}.items()),'MCP23017 SOIC pinout; GPA7/GPB7 outputs only')
    check(pins('U17')=={'1':'SAFE_CLEAR_N','2':'GND','3':'+3V3','4':'WATCHDOG','5':'+3V3'},'TPS3828 watchdog pinout')
    check(pins('U18')=={'1':'SAFE_CLEAR_N','2':'GND','3':'+3V3','4':'RESET_DELAY','5':'SENSE_5A','6':'+3V3'},'TPS3808 supply monitor pinout')
    check(all(pins('U16')[str(k)]==v for k,v in {1:'SAFE_CLEAR_N',2:'+3V3',3:'OUTPUT_PERMIT',4:'+3V3',5:'SAFE_LATCH'}.items()),'Fault latch needs a fresh permit edge')
    check(all(pins('U20')[str(k)]==v for k,v in {1:'SAFE_LATCH',2:'OUTPUT_PERMIT',3:'GND',4:'SAFE_PERMIT',5:'+3V3'}.items()),'Permit and fault latch qualify output enables')
    check(all(pins(u)[str(k)]=='SAFE_PERMIT' for u in ('U5','U6') for k in (2,5,10,13)),'All channel gates use qualified permit')
    check(pins('RPERMIT')=={'1':'OUTPUT_PERMIT','2':'GND'},'Permit defaults low')
    check(all(pins(f'RE{n}')=={'1':f'SW_ON{n}','2':'GND'} for n in range(1,9)),'All output switches default disconnected')
    check('R-78E5.0-1.0' in byid['UREG']['value'] and byid['UREG']['footprint']=='recom','Exact 1 A regulator and footprint')
    check(pins('JPOWER')=={'1':'-12_IN','2':'-12_IN','3':'GND','4':'GND','5':'GND','6':'GND','7':'GND','8':'GND','9':'+12_IN','10':'+12_IN'},'Eurorack IDC10 polarity')
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            check(p[str(src)]==port and p[str(drain)]==f'DRIVE{n}' and p[str(ctl)]==f'SW_ON{n}' and p['12']=='SAFE_CLEAR_N',f'Protected output {n}: source faces jack')
            p=pins(f'U{14+bank}')
            check(p[str(src)]==f'INPUT_LIMIT{n}' and p[str(drain)]==f'PROTECTED{n}' and p['12']=='SAFE_CLEAR_N',f'Protected input {n}: source faces jack')
    check(PINS['WATCHDOG']==24 and PINS['FAULT_N']==25 and PINS['OLED_RESET']==26,'Dedicated safety and OLED GPIO')

    metrics=json.loads((OUT/'board-metrics.json').read_text(encoding='utf-8'))
    padmaps={}
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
